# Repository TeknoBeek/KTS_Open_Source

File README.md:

# KTS_Open_Source

# Kovan Takip Sistemi Açık Kaynak Dosyaları

KTS donanım olarak açık kaynak olarak paylaşılmıştır.

Yazılım kısmında ise cihazın TEMEL ÖZELLİKLERİNİ kullanabileceğiniz bir bedava bir sürüm (firmware) bulunmaktadır.

Profesyonel ve TAM SÜRÜME ileride küçük bir ücret mukabili geçilebilecektir.

KTS piyasada hazır olarak kolayca bulunabilecek modüller kullanılarak geliştirildi. 

Yani sonuçta AMATÖR bir cihaz olacak.

Bu yüzden de TR'de ve dünyada muhtemelen en ucuza mal edilebilecek bir veri kaydedici olacaktır.

AMATÖR bir cihaz olmasına rağmen kullanılacak alan için profesyonele yakın bir çözüm sunmaktadır. 

Ve 5 yıla aşkın saha kullanımında da gayet yeterli olduğunu kanıtlamıştır.

Bu cihazın amatör şartlar dahilinde geliştirildiğini unutmamanızı tavsiye ederim.

Bu yüzden doğabilecek olumsuzluklar hakkında hiç bir şekilde sorumluluk almam. 

Yalnız cihazın ARICILIK ile ilgili bölümündeki tasarım, 20 seneyi aşkın arıcılık geçmişim sayesinde olmuştur.

Hangi sensörlerin kullanılması gerekliliği, nerede kullanılacağı,

nelerin takip edileceği, verilerin nasıl analiz edileceği vb. konular bu sebeple yabancısı olmadığım konular.

6 seneyi aşkın bir süre içinde gelişe gelişe cihaz bugünkü haline evrildi.

KTS nedir tanıtım PDF'inde de bahsedildiği gibi bu cihaz aslında bir veri toplayıcı. 

Arıcılık sektöründe kullanılabileceği gibi SERACILIK, SULAMA, KÜMES OTOMASYONU, EV OTOMASYONU, HAVA İSTASYONU vb. 

bir çok alanda da kullanılabilecek şekilde, modüler bir biçimde yapıldı.

Farklı bir alanda kullanmak için ilgili modülü konnektörden ekleyip, o modulün

yazılımını yüklemek yeterli olacak.

Bundan sonraki tüm yazılımlar bu donanım ile uyumlu olacak.

İlerleyen zamanlarda www.akıllıkovan.com veya GitHub üzerinden bu yazılımlara ulaşmak mümkün olacak.

# NASIL BİR YOL İZLENECEK

Öncelikle www.akıllıkovan.com web sitesi dökümantasyon için kullanılacak.

GitHub adresinde de yine yapım bilgilerini içeren PDF dosyaları, PCB dosyaları (Gerber ve BRD) , ve YAZILIM Firmware bulunacak.

Youtube kanalında ise hem tanıtım videoları hem de yapım aşamalarını gösteren kısa ve uzun videolar bulanacak. Bu sebeple kanala abone olmanızı tavsiye ederim. https://www.youtube.com/c/TeknoBeek

------------------------------------------------------------------------------------

# KİMLER YAPABİLİR ?

Temel seviyede elektronik bilgisi olan herkes yapabilir.

Bilinmesi gereken konular;

Kart dizilimi ve lehimleme, (kablo lehimleme - bağlama vb. dahil)

PCB'yi kendi yapacaksa ev yapımı PCB bilgisine haiz olmak,

Mikroişlemciye yazılım atmak.

Montaj konusundaki delme, yapıştırma vb. el işçiliği.

Arıcılar yarı marangoz olduğu için en kolay kısım burası olacaktır.

Kendiniz yapamadığınız takdirde meslek lisesinde bulunan bir çocuk bile muhtemelen bunları yapabilecektir.

-------------------------------------------------------------------------------------

# PARÇALAR NEREDEN TEMİN EDİLECEK ?

Elektronik parçaların hepsi ister yurtiçinden isten yurtdışından kolaylıkla bulunabilecek şekilde tasarlandı.

Türkiye'de online alışveriş yapılabilen büyük firmaların birisinden hepsi temin edilebilir.

Elektronik kısmına ait liste sitede bulunmaktadır.

Kutu seçimi isteğe bağlı olmakla beraber açık kaynaktaki kutu TR'deki bir firmadan temin edilebilir.

Plastik parçalar özel üretim olduğu için muhtemelen bu projenin en zor bulunacak bölümünü oluşturuyor.

3D çizim dosyaları thingiverse hesabımdan indirilip 3D yazıcıda yazdırılabilir.

Bu hesapta da 3D klasöründe STL dosyaları bulunmaktadır.

Baskı almak için Türkiye'de 3D baskı yapan firmalar var.

Bu konuda ben de yardımcı olmaya çalışırım.

PCB konusunda kendi yapabilecek veya birine yaptırabilecek kimseler için çizim dosyaları bu hesapta bulunacaktır.

Profesyonel firma üretimi olan PCB'ler (Çin) elimde fazla bulunduğu takdirde

bu konuda da yardımcı olabilirim.

Plastik Altlık kullanılacak ise kullanılacak altlığın modeli sitede yazmaktadır.

Tüm 3D plastik parçalar bu model altlığa göredir.

Altlık kullanılmayıp onun yerine bir platform kullanılacaksa bununla ilgili de 3D çizimler ayrıca verilmiştir.

Piyasadan hazır dijital kantar kullanımı ile ilgili bilgi notu yakında paylaşılacaktır.

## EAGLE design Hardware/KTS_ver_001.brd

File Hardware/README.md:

# KTS PCB 

Güncelleme: 
V_002 yüklendi. SE-222 Kodlu kutuya uygun olarak dizayn edildi. 
V_002 klasöründe gerber dosyaları mevcut. Testleri yapıldı
-------------------------------------------------------------
Önemli not ! 

Donanım ve yazılım konusunda formal bir eğitimim yoktur. 
Hobi amaçlı ve amatör ruhla geliştirilmeye çalışılmıştır. 
Bunun göz önünde tutulması rica olunur. 

Versiyon1 evde de imal edilebilmesi amacıyla ağırlıklı olarak tek yüzlü olarak tasarlandı. 
Sadece birkaç köprü kablo ile çalıştırılabilmektedir. 
Ütü, aseton vb. ev tipi tekniklerle imal edilebilir. 
Ev tipi üretim konusunda yönlendirme yapabilirim. 

Çin'den veya TR'deki bir firma üzerinden üretim yaptırmak isterseniz 
gerekli gerber dosyaları da buradadır. 
Ben bu dosyalar ile Çin üzerinden bir firma ile PCB yaptırdım. 
Elimde fazla olduğu takdirde PCB temini konusunda da yardımcı olabilirim. 

Bu dizindeki BOM dosyası Eagle CAM'in kendi çıkardığı dosyadır. 
Daha detaylı bilgiye PDF dizinindeki malzemeler dosyasından ulaşabilirsiniz.

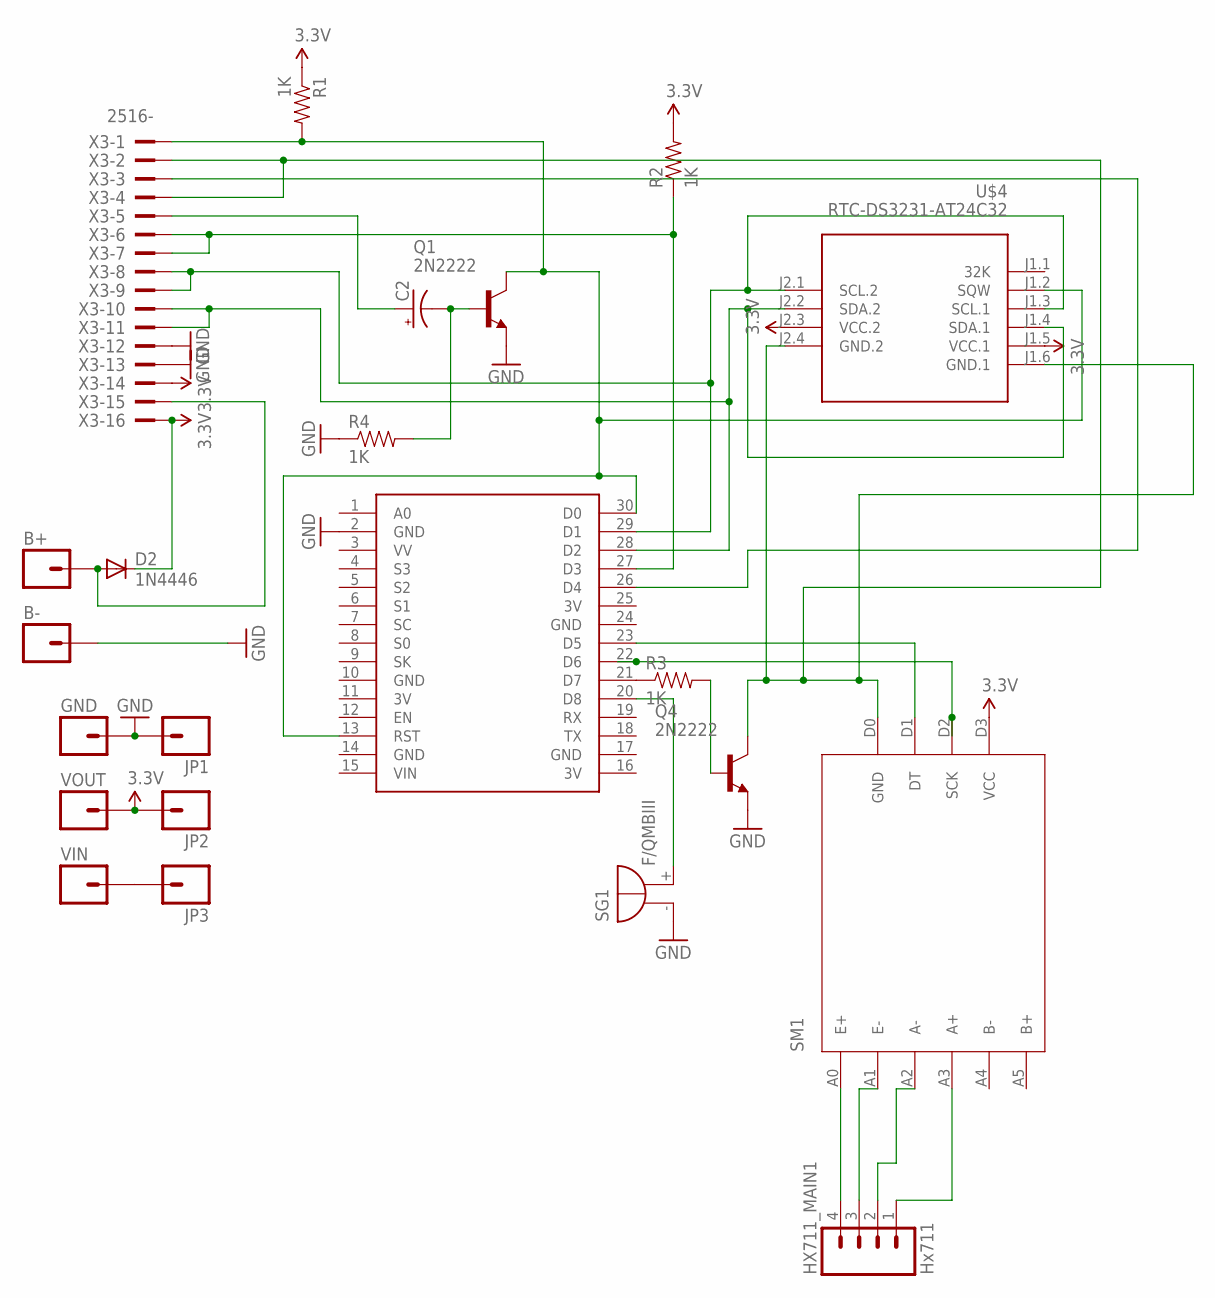
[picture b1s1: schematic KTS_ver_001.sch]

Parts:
B+: M01OFFSET; 1X01_OFFSET
B-: M01OFFSET; 1X01_OFFSET
C2: CAP_POLPTH2; CPOL-RADIAL-10UF-25V
D2: 1N4446; DO35-10
GND: M01PTH; 1X01
HX711_MAIN1: Hx711; 1X04_LOCK
JP1, JP2, JP3: M01PTH; 1X01
Q1, Q4: 2N2222; TO18
R1, R2, R3, R4: 1K; AXIAL-0.3
SG1: F/QMBIII
SM1: HX711
U$3: NODEMCU
U$4: RTC-DS3231-AT24C32
VIN: M01PTH; 1X01
VOUT: M01PTH; 1X01
X3: 2516-; PAK100/2500-16

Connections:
3.3V: D2.C, JP2.1, R1.P$1 (1), R2.P$2 (2), SM1.D3 (VCC), U$4.J1.5 (VCC.1), U$4.J2.3 (VCC.2), VOUT.1, X3.14, X3.16
3V: U$3.11 (3V), U$3.16 (3V), U$3.25 (3V)
BUTTON/D1: U$3.26 (D4), X3.3
D7: R3.P$1 (1), U$3.21 (D7)
D8/BUZZER1: SG1.+ (-), U$3.20 (D8)
DS18B20/D1: R2.P$1 (1), U$3.27 (D3), X3.6, X3.7
GND: B-.1, GND.1, JP1.1, Q1.1 (E), Q4.1 (E), R4.P$1 (1), SG1.- (+), U$3.2 (GND), U$3.10 (GND), U$3.14 (GND), U$3.17 (GND), U$3.24 (GND), X3.12, X3.13
HX711/DT/D5: SM1.D1 (DT), U$3.23 (D5)
LOADBUS1: Q4.3 (C), SM1.D0 (GND), U$4.J1.6 (GND.1), U$4.J2.4 (GND.2), X3.2, X3.4
unnamed: B+.1, D2.A, X3.15
unnamed: C2.2 (-), Q1.2 (B), R4.P$2 (2)
unnamed: Q4.2 (B), R3.P$2 (2)
unnamed: JP3.1, VIN.1
unnamed: HX711_MAIN1.4, SM1.A0 (E+)
unnamed: HX711_MAIN1.3, SM1.A1 (E-)
unnamed: HX711_MAIN1.2, SM1.A2 (A-)
unnamed: HX711_MAIN1.1, SM1.A3 (A+)
RESET_BUS1: Q1.3 (C), R1.P$2 (2), U$3.13 (RST), U$3.30 (D0), U$4.J1.2 (SQW), X3.1
SCK/D6/HX711: SM1.D2 (SCK), U$3.22 (D6)
SCL/D2: U$3.29 (D1), U$4.J1.3 (SCL.1), U$4.J2.1 (SCL.2), X3.8, X3.9
SDA/D1: U$3.28 (D2), U$4.J1.4 (SDA.1), U$4.J2.2 (SDA.2), X3.10, X3.11
SIGNAL(RESET): C2.1 (+), X3.5

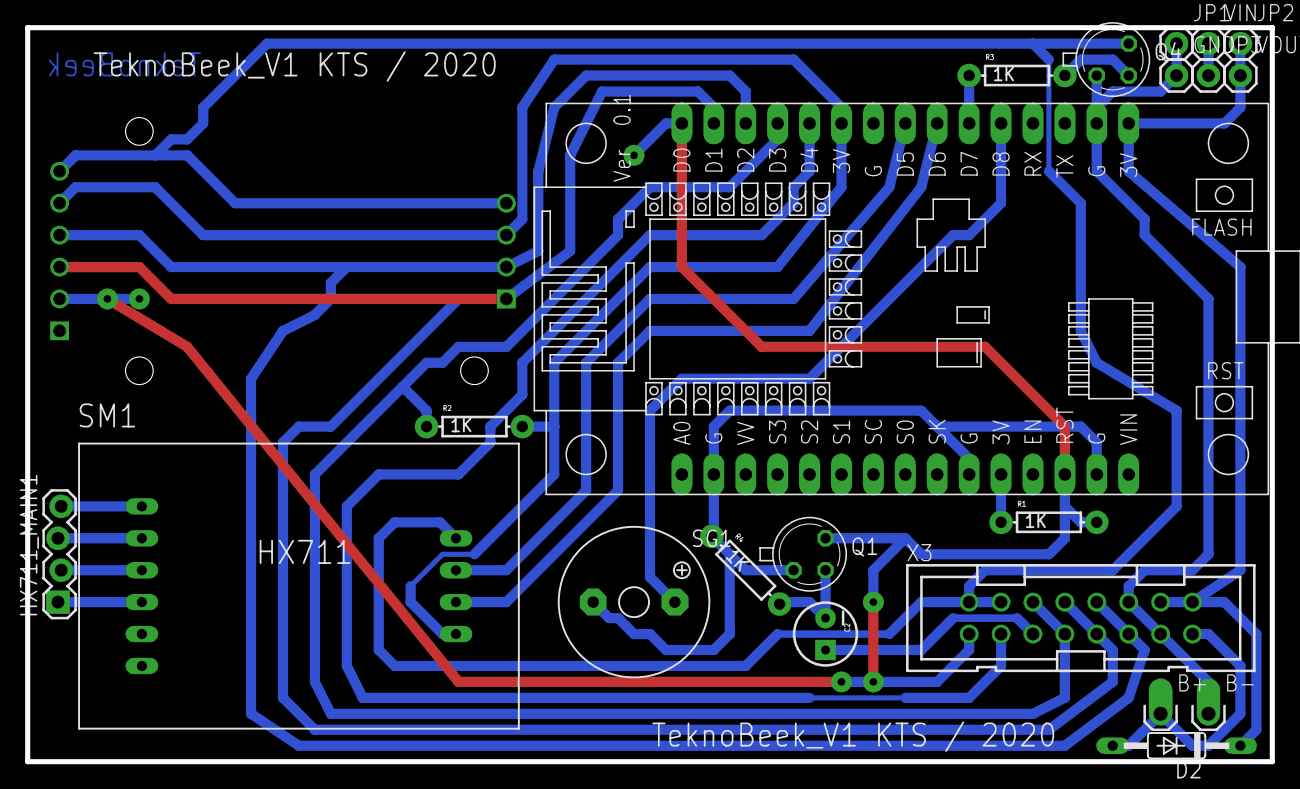
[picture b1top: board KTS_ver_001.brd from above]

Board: 2 copper layers, 99.1 x 58.4 mm, 22 parts (1 on the bottom side), 22 nets.

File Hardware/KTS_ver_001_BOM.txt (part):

Partlist exported from C:/Users/User/Desktop/Happy_final_001.sch at 13.03.2022 03:56:31

Part        Value              Device             Package              Description                                                                                                                                                                                                                                                                                                                                                                                                                                                                                                                                                                   MF MPN OC_FARNELL OC_NEWARK PROD_ID   VALUE
B+                             M01OFFSET          1X01_OFFSET          Header 1                                                                                                                                                                                                                                                                                                                                                                                                                                                                                                                                                                                                                 
B-                             M01OFFSET          1X01_OFFSET          Header 1                                                                                                                                                                                                                                                                                                                                                                                                                                                                                                                                                                                                                 
C2                             CAP_POLPTH2        CPOL-RADIAL-10UF-25V Capacitor Polarized                                                                                                                                                                                                                                                                                                                                                                                                                                                                                                                                                                                                      
D2          1N4446             1N4446             DO35-10              DIODE                                                                                                                                                                                                                                                                                                                                                                                                                                                                                                                                                                                                                    
GND                            M01PTH             1X01                 Header 1                                                                                                                                                                                                                                                                                                                                                                                                                                                                                                                                                                                                                 
HX711_MAIN1 Hx711              M04LOCK            1X04_LOCK            Header 4                                                                                                                                                                                                                                                                                                                                                                                                                                                                                                                                                                                                                 
JP1                            M01PTH             1X01                 Header 1                                                                                                                                                                                                                                                                                                                                                                                                                                                                                                                                                                                                                 
JP2                            M01PTH             1X01                 Header 1                                                                                                                                                                                                                                                                                                                                                                                                                                                                                                                                                                                                                 
JP3                            M01PTH             1X01                 Header 1                                                                                                                                                                                                                                                                                                                                                                                                                                                                                                                                                                                                                 
Q1          2N2222             2N2222             TO18                 NPN Transistor                                                                                                                                                                                                                                                                                                                                                                                                                                                                                                                                                                                                           
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
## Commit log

2022-03-19 resize
2022-03-19 resized2
2022-03-19 3Dfiles
2022-03-19 read
2022-03-19 taban
2022-03-20 V_001
2022-03-26 V_002

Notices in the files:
parts and their libraries:
SparkFun-Connectors: Licensing: Creative Commons ShareAlike 4.0 International - https://creativecommons.org/licenses/by-sa/4.0
diy-modules: Released under the Creative Commons Attribution 4.0 International License: http://creativecommons.org/licenses/by/4.0
